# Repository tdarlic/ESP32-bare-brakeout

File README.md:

# ESP8266 bare brakeout board
This is the brakeout board created in KiCad for the MKS Nano 3D printing board. 
The brakeout board intended to be DIY etched and produced at home

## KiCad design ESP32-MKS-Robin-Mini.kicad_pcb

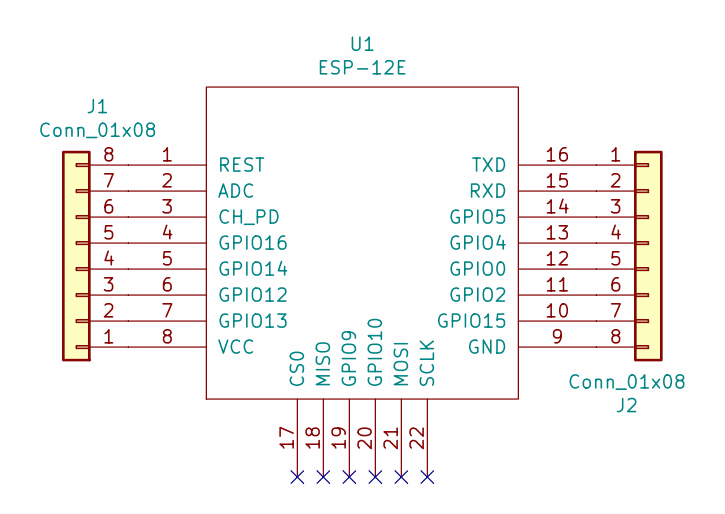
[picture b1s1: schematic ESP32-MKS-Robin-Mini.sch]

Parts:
J1, J2: Conn_01x08; Pin_Header_Straight_1x08_Pitch2.54mm
U1: ESP-12E; ESP-12E_SMD

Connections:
unnamed: J1.1, U1.8 (VCC)
unnamed: J1.2, U1.7 (GPIO13)
unnamed: J1.3, U1.6 (GPIO12)
unnamed: J1.4, U1.5 (GPIO14)
unnamed: J1.5, U1.4 (GPIO16)
unnamed: J1.6, U1.3 (CH_PD)
unnamed: J1.7, U1.2 (ADC)
unnamed: J1.8, U1.1 (REST)
unnamed: J2.1, U1.16 (TXD)
unnamed: J2.2, U1.15 (RXD)
unnamed: J2.3, U1.14 (GPIO5)
unnamed: J2.4, U1.13 (GPIO4)
unnamed: J2.5, U1.12 (GPIO0)
unnamed: J2.6, U1.11 (GPIO2)
unnamed: J2.7, U1.10 (GPIO15)
unnamed: J2.8, U1.9 (GND)

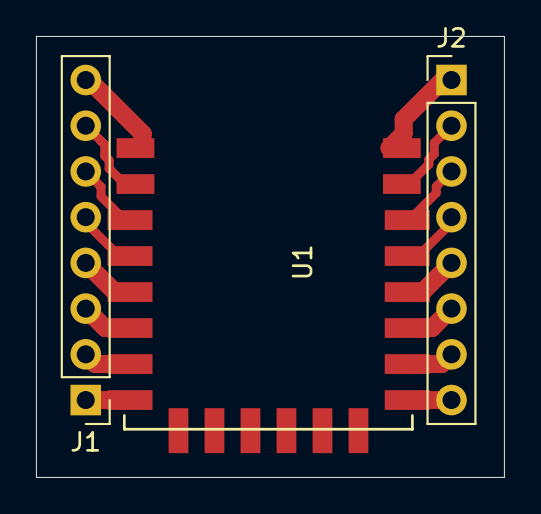
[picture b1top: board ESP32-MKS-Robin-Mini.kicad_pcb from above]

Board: 2 copper layers, 26.0 x 24.5 mm, 3 parts (0 on the bottom side), 16 nets.
